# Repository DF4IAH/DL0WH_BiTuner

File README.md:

# DL0WH_BiTuner_Firmware
Based on the DJ0ABR tuner hardware this project is a replacement for the controller PCB and its firmware. The new PCB does have a __STM32L476RGT6__ MCU device and has got preparations for SWR metering.

## V1.2 PCB after placement and routing was done:

## V1.2 MCU Pinout:

## Ready for samples:
The board is again ready for production.

## Version list:
V1.2 SWD connector bad size - 2019-02-01
* Library content for the CORTEX JTAG/SWD connector was wrong, fixed.
* PCB board house failed on trace distances of 6 mils. Design expanded to 8 mils.

---

V1.1 LQFP64 bug fix - 2019-01-18
* Due to a bad LQFP64 package within the STM32L4 library (who made that crappy library?) the device did not fit at the PCB. That made a turn-around to take time and money. Never trust any library again.

---

V1.0 initial version - 2019-01-04

---

73  Uli DF4IAH, Ladenburg, 2019-02-01

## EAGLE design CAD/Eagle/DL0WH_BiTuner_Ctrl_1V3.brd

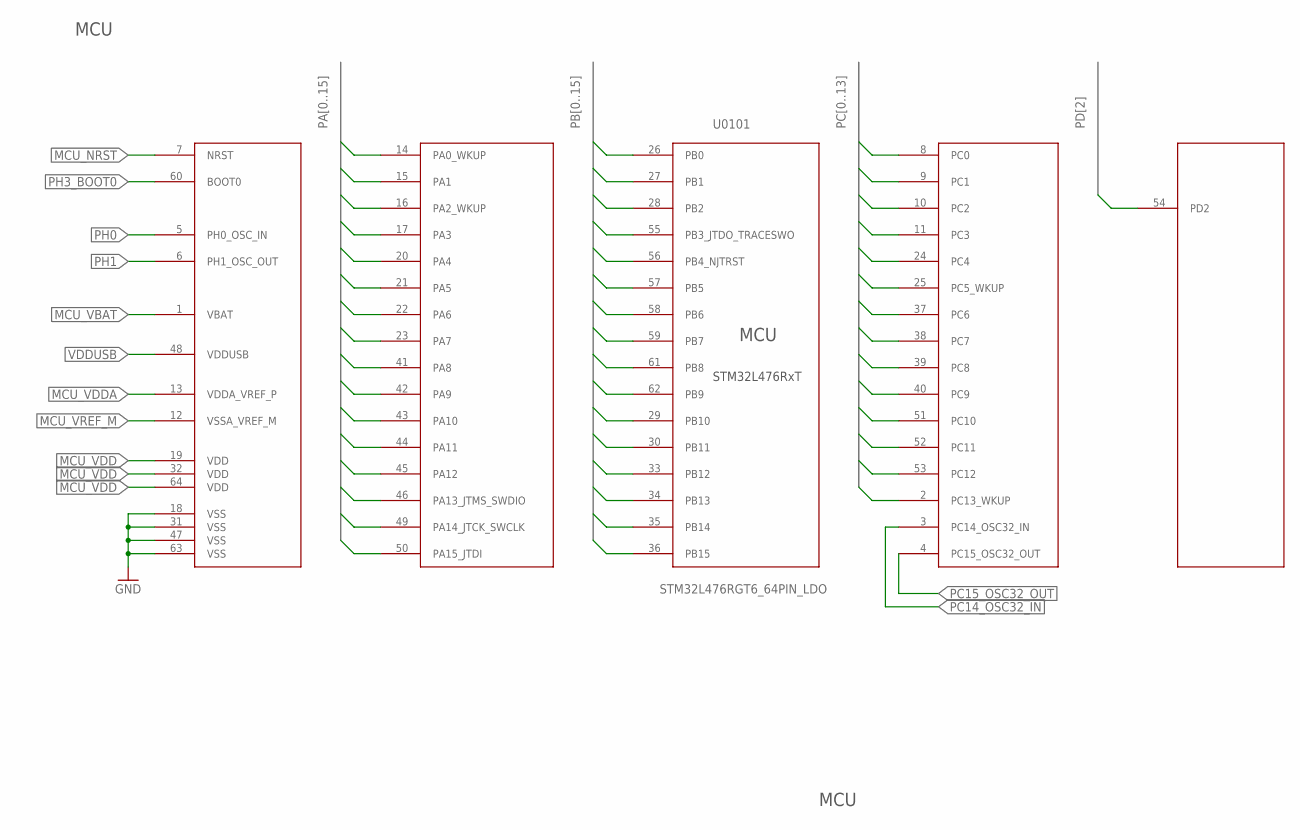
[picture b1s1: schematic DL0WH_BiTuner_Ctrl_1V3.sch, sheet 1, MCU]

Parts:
U0101: STM32L476RGT6_64PIN_LDO; LQFP64

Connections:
GND: U0101.18 (VSS), U0101.31 (VSS), U0101.47 (VSS), U0101.63 (VSS); also elsewhere on the board
MCU_NRST: U0101.7 (NRST); also elsewhere on the board
MCU_VBAT: U0101.1 (VBAT); also elsewhere on the board
MCU_VDD: U0101.19 (VDD), U0101.32 (VDD), U0101.64 (VDD); also elsewhere on the board
MCU_VDDA: U0101.13 (VDDA_VREF_P); also elsewhere on the board
MCU_VREF_M: U0101.12 (VSSA_VREF_M); also elsewhere on the board
PA0: U0101.14 (PA0_WKUP); also elsewhere on the board
PA1: U0101.15 (PA1); also elsewhere on the board
PA2: U0101.16 (PA2_WKUP)
PA3: U0101.17 (PA3); also elsewhere on the board
PA4: U0101.20 (PA4)
PA5: U0101.21 (PA5); also elsewhere on the board
PA6: U0101.22 (PA6); also elsewhere on the board
PA7: U0101.23 (PA7); also elsewhere on the board
PA8: U0101.41 (PA8)
PA9: U0101.42 (PA9); also elsewhere on the board
PA10: U0101.43 (PA10); also elsewhere on the board
PA11: U0101.44 (PA11); also elsewhere on the board
PA12: U0101.45 (PA12); also elsewhere on the board
PA13: U0101.46 (PA13_JTMS_SWDIO); also elsewhere on the board
PA14: U0101.49 (PA14_JTCK_SWCLK); also elsewhere on the board
PA15: U0101.50 (PA15_JTDI); also elsewhere on the board
PB0: U0101.26 (PB0); also elsewhere on the board
PB1: U0101.27 (PB1); also elsewhere on the board
PB2: U0101.28 (PB2); also elsewhere on the board
PB3: U0101.55 (PB3_JTDO_TRACESWO)
PB4: U0101.56 (PB4_NJTRST)
PB5: U0101.57 (PB5)
PB6: U0101.58 (PB6); also elsewhere on the board
PB7: U0101.59 (PB7); also elsewhere on the board
PB8: U0101.61 (PB8)
PB9: U0101.62 (PB9); also elsewhere on the board
PB10: U0101.29 (PB10); also elsewhere on the board
PB11: U0101.30 (PB11); also elsewhere on the board
PB12: U0101.33 (PB12); also elsewhere on the board
PB13: U0101.34 (PB13); also elsewhere on the board
PB14: U0101.35 (PB14)
PB15: U0101.36 (PB15)
PC0: U0101.8 (PC0); also elsewhere on the board
PC1: U0101.9 (PC1); also elsewhere on the board
PC2: U0101.10 (PC2); also elsewhere on the board
PC3: U0101.11 (PC3); also elsewhere on the board
PC4: U0101.24 (PC4); also elsewhere on the board
PC5: U0101.25 (PC5_WKUP)
PC6: U0101.37 (PC6)
PC7: U0101.38 (PC7)
PC8: U0101.39 (PC8)
PC9: U0101.40 (PC9)
PC10: U0101.51 (PC10)
PC11: U0101.52 (PC11)
PC12: U0101.53 (PC12)
PC13: U0101.2 (PC13_WKUP)
PC14_OSC32_IN: U0101.3 (PC14_OSC32_IN); also elsewhere on the board
PC15_OSC32_OUT: U0101.4 (PC15_OSC32_OUT); also elsewhere on the board
PD2: U0101.54 (PD2)
PH0: U0101.5 (PH0_OSC_IN)
PH1: U0101.6 (PH1_OSC_OUT)
PH3_BOOT0: U0101.60 (BOOT0); also elsewhere on the board
VDDUSB: U0101.48 (VDDUSB); also elsewhere on the board

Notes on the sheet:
STM32L476RxT
MCU

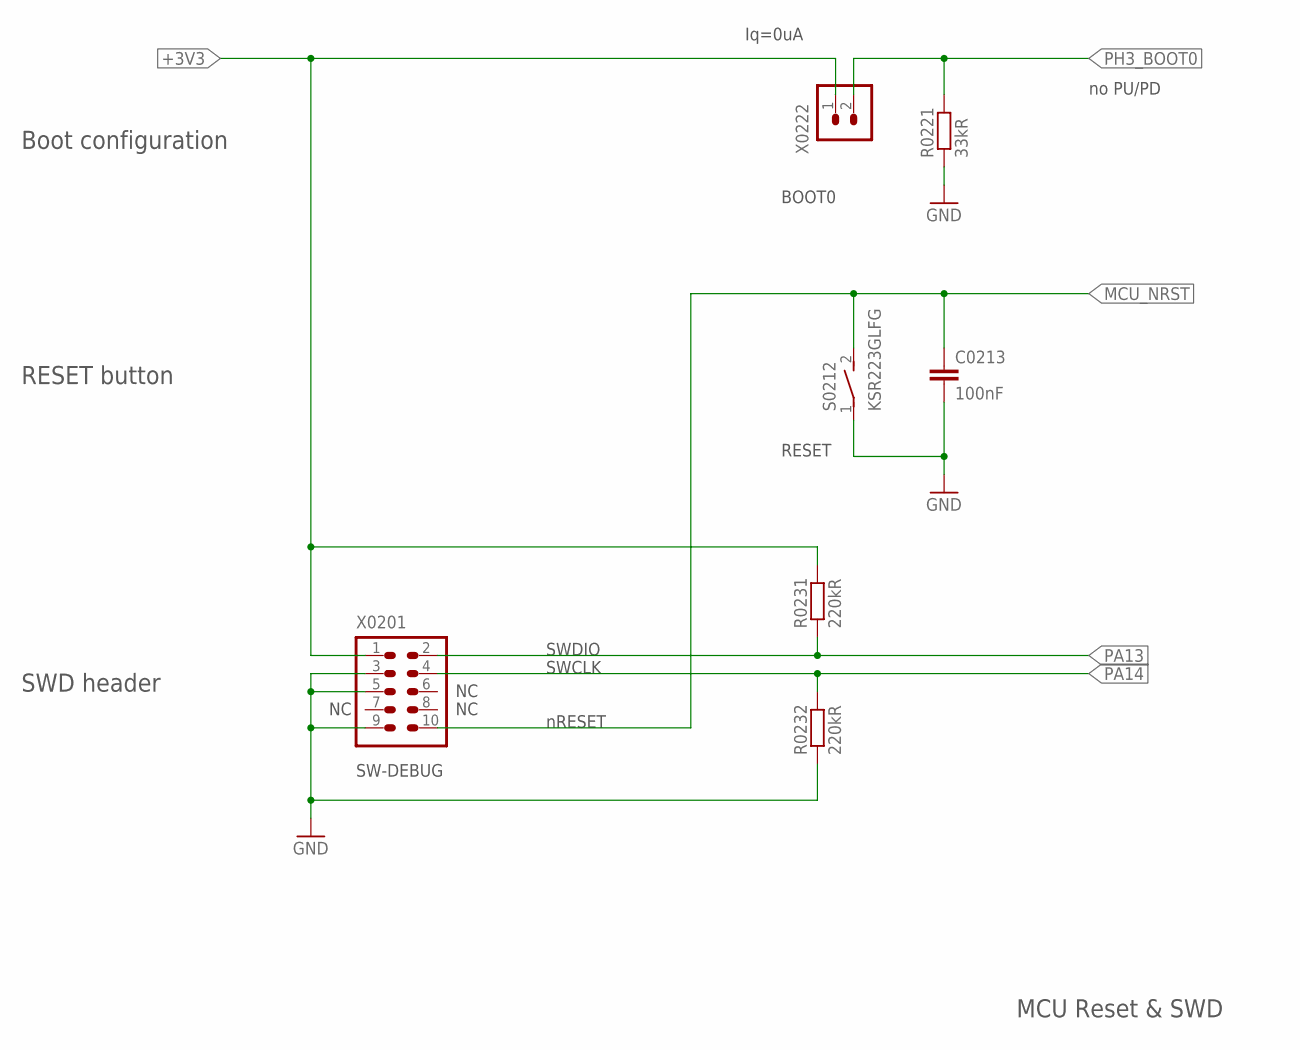
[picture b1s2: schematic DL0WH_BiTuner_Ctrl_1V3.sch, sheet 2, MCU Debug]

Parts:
C0213: 100nF; C0402
R0221: 33kR; R0402
R0231, R0232: 220kR; R0402
S0212: KSR223GLFG; KSR223G_SMD_1POL
X0201: FTSH-105-01-F-D-K; 2X05_1MM27_SHROUDED_CORTEX_JTAG_SWD
X0222: HEADER-1X2; 1X02

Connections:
+3V3: R0231.2, X0201.1, X0222.1; also elsewhere on the board
GND: C0213.2, R0221.1, R0232.1, S0212.1, X0201.3, X0201.5, X0201.9; also elsewhere on the board
MCU_NRST: C0213.1, S0212.2 (S), X0201.10; also elsewhere on the board
PA13: R0231.1, X0201.2; also elsewhere on the board
PA14: R0232.2, X0201.4; also elsewhere on the board
PH3_BOOT0: R0221.2, X0222.2; also elsewhere on the board

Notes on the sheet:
SWDIO
SWCLK
RESET
BOOT0
SW-DEBUG
SWD header
Boot configuration
RESET button
nRESET
MCU Reset & SWD
no PU/PD
Iq=0uA

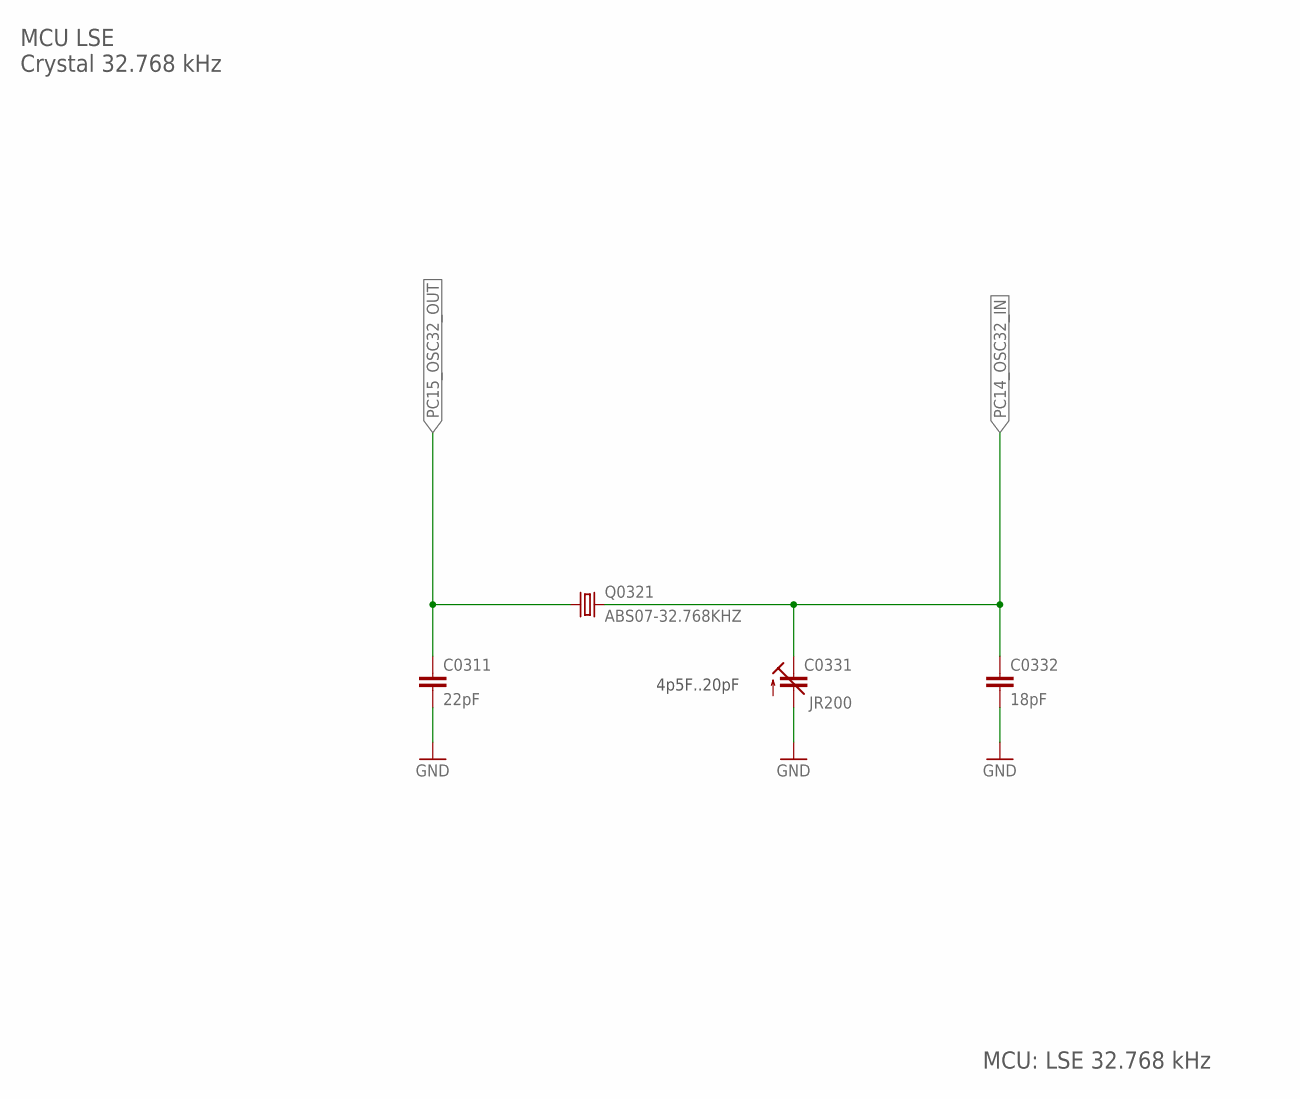
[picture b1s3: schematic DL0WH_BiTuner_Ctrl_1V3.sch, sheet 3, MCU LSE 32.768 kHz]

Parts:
C0311: 22pF; C0402
C0331: JR200; 3MM2_X_2MM5
C0332: 18pF; C0402
Q0321: ABS07-32.768KHZ; ABS07

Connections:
GND: C0311.2, C0331.+ (A), C0332.2; also elsewhere on the board
PC14_OSC32_IN: C0331.- (E), C0332.1, Q0321.2; also elsewhere on the board
PC15_OSC32_OUT: C0311.1, Q0321.1; also elsewhere on the board

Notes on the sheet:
4p5F..20pF
MCU LSE Crystal 32.768 kHz
MCU: LSE 32.768 kHz

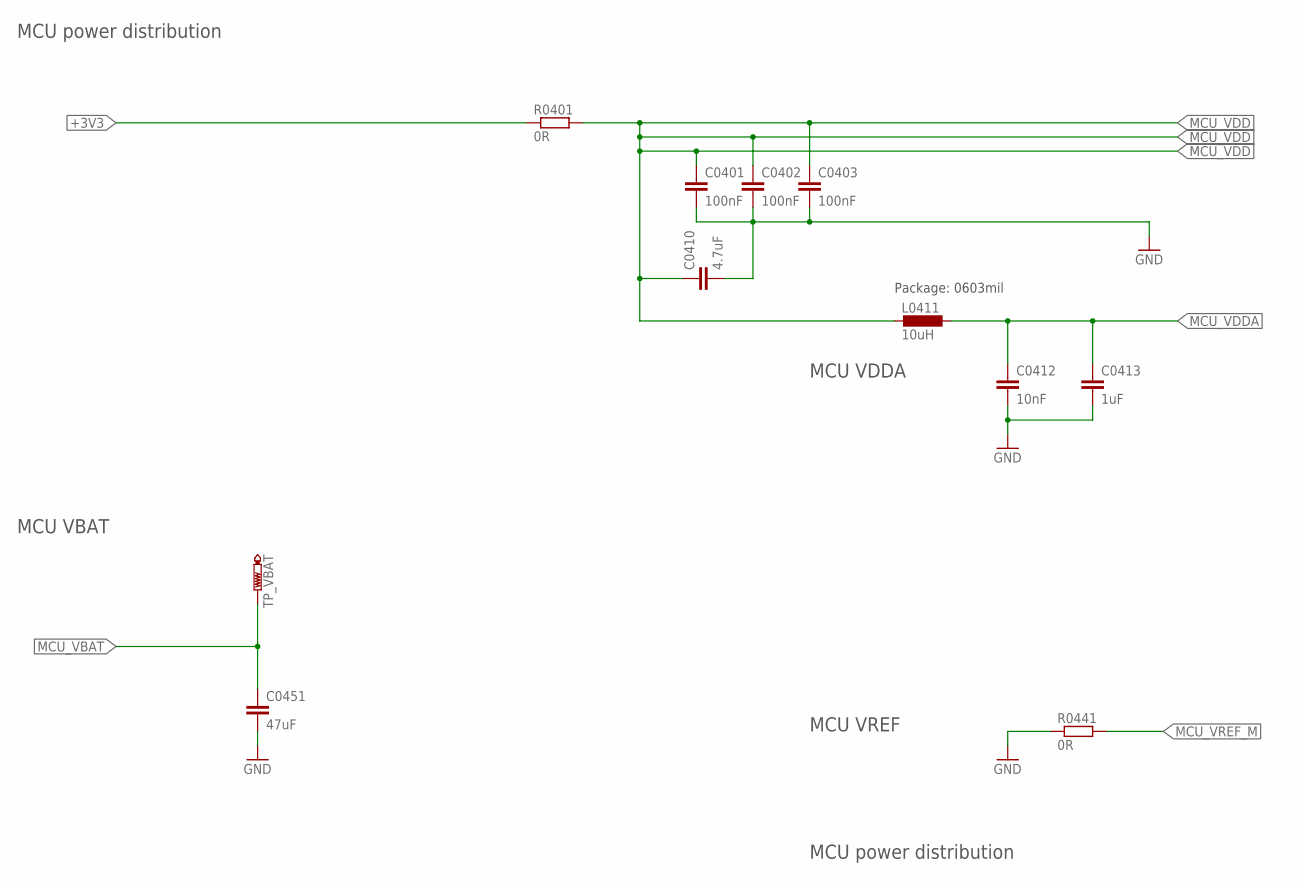
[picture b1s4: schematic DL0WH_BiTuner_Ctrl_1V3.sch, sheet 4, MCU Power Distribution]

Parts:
C0401, C0402, C0403: 100nF; C0402
C0410: 4.7uF; C0603
C0412: 10nF; C0402
C0413: 1uF; C0402
C0451: 47uF; C0805
L0411: 10uH; L0603
R0401, R0441: 0R; R0402
TP_VBAT: PTR1B1,27; B1,27

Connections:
+3V3: R0401.1; also elsewhere on the board
GND: C0401.2, C0402.2, C0403.2, C0410.2, C0412.2, C0413.2, C0451.2, R0441.1; also elsewhere on the board
MCU_VBAT: C0451.1, TP_VBAT.TP; also elsewhere on the board
MCU_VDD: C0401.1, C0402.1, C0403.1, C0410.1, L0411.1, R0401.2; also elsewhere on the board
MCU_VDDA: C0412.1, C0413.1, L0411.2; also elsewhere on the board
MCU_VREF_M: R0441.2; also elsewhere on the board

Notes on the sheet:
MCU VDDA
MCU VREF
MCU VBAT
MCU power distribution
Package: 0603mil

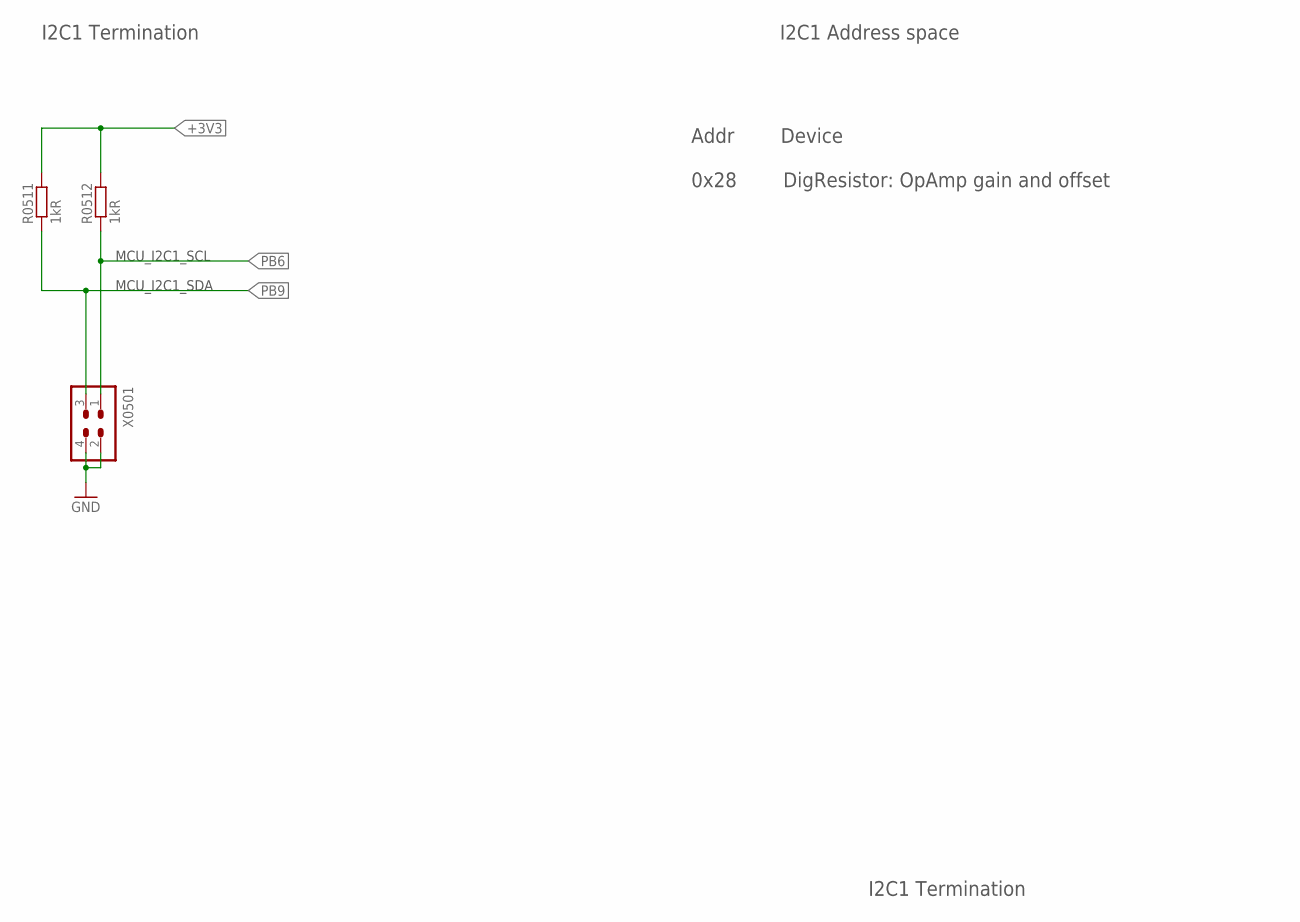
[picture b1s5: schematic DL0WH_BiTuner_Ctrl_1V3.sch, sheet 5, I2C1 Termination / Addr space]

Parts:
R0511, R0512: 1kR; R0402
X0501: HEADER-2X2; 2X02

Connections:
+3V3: R0511.2, R0512.2; also elsewhere on the board
GND: X0501.2, X0501.4; also elsewhere on the board
PB6: R0512.1, X0501.1; also elsewhere on the board
PB9: R0511.1, X0501.3; also elsewhere on the board

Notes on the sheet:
Addr Device 0x28 DigResistor: OpAmp gain and offset
I2C1 Termination
I2C1 Address space
MCU_I2C1_SCL
MCU_I2C1_SDA

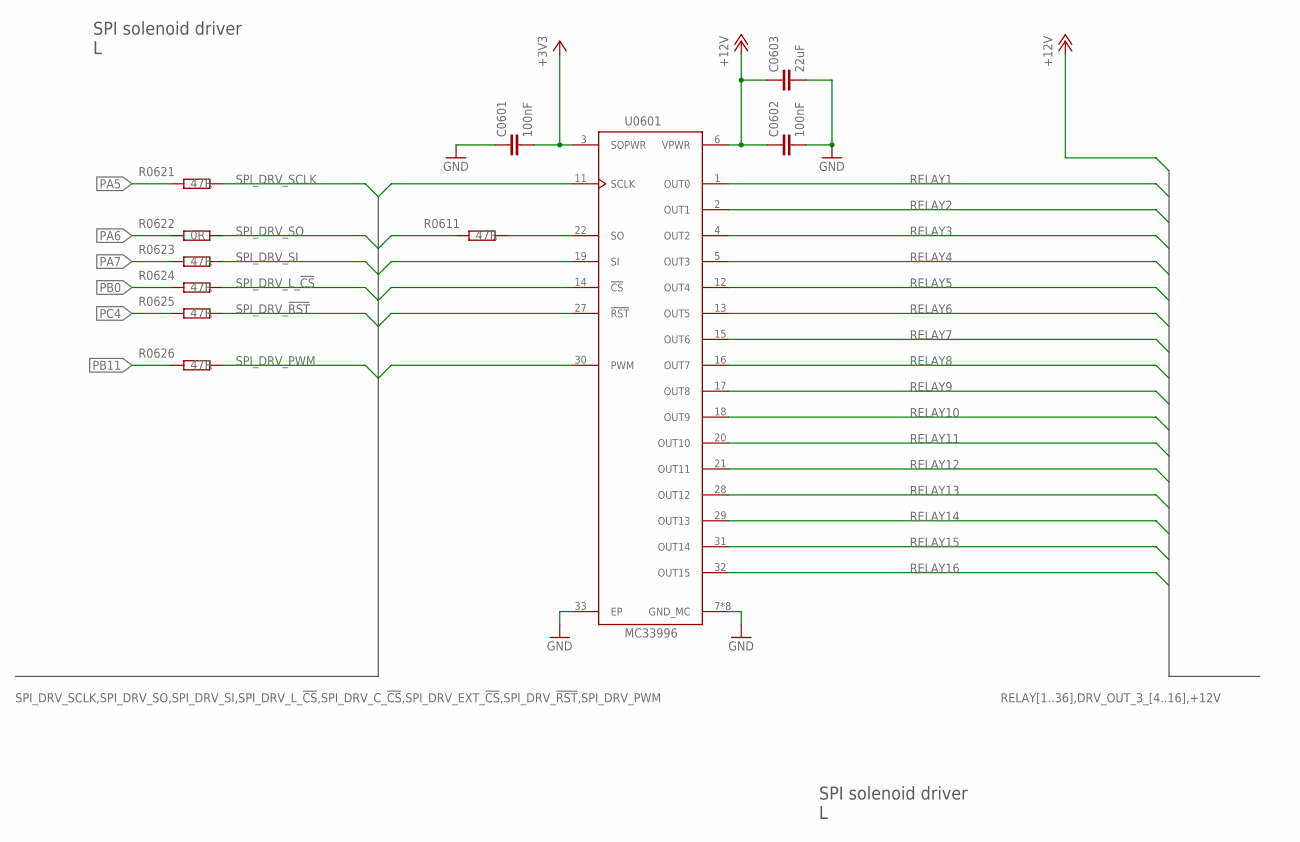
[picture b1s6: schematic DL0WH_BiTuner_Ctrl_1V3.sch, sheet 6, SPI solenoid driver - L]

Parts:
C0601, C0602: 100nF; C0402
C0603: 22uF; C0603
R0611, R0621, R0623, R0624, R0625, R0626: 47R; R0402
R0622: 0R; R0402
U0601: MC33996; SOICW32

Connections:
+3V3: C0601.2, U0601.3 (SOPWR); also elsewhere on the board
+12V: C0602.1, C0603.1, U0601.6 (VPWR); also elsewhere on the board
GND: C0601.1, C0602.2, C0603.2, U0601.7 (GND_MC), U0601.8 (GND_MC), U0601.9 (GND_MC), U0601.10 (GND_MC), U0601.23 (GND_MC), U0601.24 (GND_MC), U0601.25 (GND_MC), U0601.26 (GND_MC), U0601.33 (EP); also elsewhere on the board
unnamed: R0611.2, U0601.22 (SO)
PA5: R0621.1; also elsewhere on the board
PA6: R0622.1; also elsewhere on the board
PA7: R0623.1; also elsewhere on the board
PB0: R0624.1; also elsewhere on the board
PB11: R0626.1; also elsewhere on the board
PC4: R0625.1; also elsewhere on the board
RELAY1: U0601.1 (OUT0); also elsewhere on the board
RELAY2: U0601.2 (OUT1); also elsewhere on the board
RELAY3: U0601.4 (OUT2); also elsewhere on the board
RELAY4: U0601.5 (OUT3); also elsewhere on the board
RELAY5: U0601.12 (OUT4); also elsewhere on the board
RELAY6: U0601.13 (OUT5); also elsewhere on the board
RELAY7: U0601.15 (OUT6); also elsewhere on the board
RELAY8: U0601.16 (OUT7); also elsewhere on the board
RELAY9: U0601.17 (OUT8); also elsewhere on the board
RELAY10: U0601.18 (OUT9); also elsewhere on the board
RELAY11: U0601.20 (OUT10); also elsewhere on the board
RELAY12: U0601.21 (OUT11); also elsewhere on the board
RELAY13: U0601.28 (OUT12); also elsewhere on the board
RELAY14: U0601.29 (OUT13); also elsewhere on the board
RELAY15: U0601.31 (OUT14); also elsewhere on the board
RELAY16: U0601.32 (OUT15); also elsewhere on the board
SPI_DRV_!RST: R0625.2, U0601.27 (!RST); also elsewhere on the board
SPI_DRV_L_!CS: R0624.2, U0601.14 (!CS)
SPI_DRV_PWM: R0626.2, U0601.30 (PWM); also elsewhere on the board
SPI_DRV_SCLK: R0621.2, U0601.11 (SCLK); also elsewhere on the board
SPI_DRV_SI: R0623.2, U0601.19 (SI); also elsewhere on the board
SPI_DRV_SO: R0611.1, R0622.2; also elsewhere on the board

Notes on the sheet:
SPI solenoid driver L

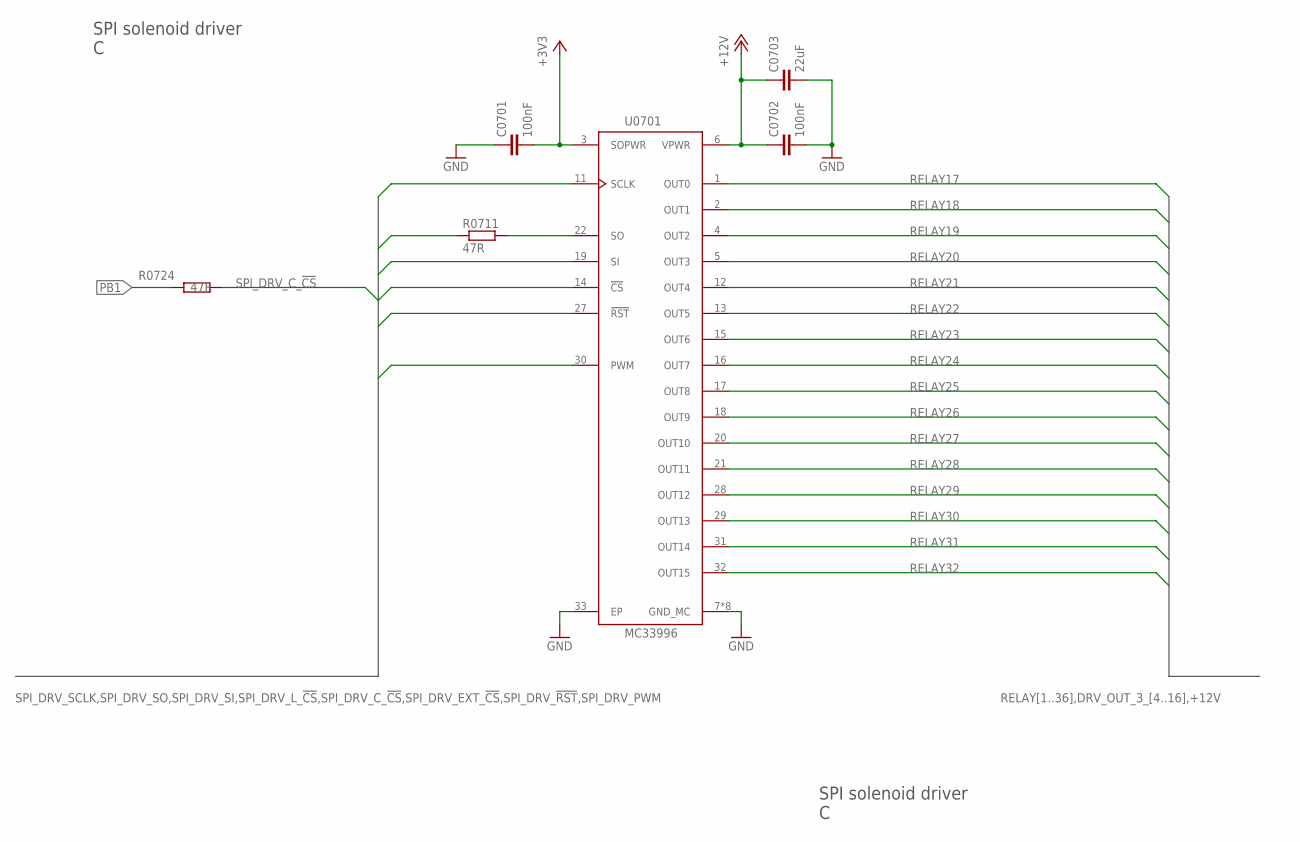
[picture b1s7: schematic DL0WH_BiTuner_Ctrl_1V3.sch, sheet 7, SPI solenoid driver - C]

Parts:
C0701, C0702: 100nF; C0402
C0703: 22uF; C0603
R0711, R0724: 47R; R0402
U0701: MC33996; SOICW32

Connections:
+3V3: C0701.2, U0701.3 (SOPWR); also elsewhere on the board
+12V: C0702.1, C0703.1, U0701.6 (VPWR); also elsewhere on the board
GND: C0701.1, C0702.2, C0703.2, U0701.7 (GND_MC), U0701.8 (GND_MC), U0701.9 (GND_MC), U0701.10 (GND_MC), U0701.23 (GND_MC), U0701.24 (GND_MC), U0701.25 (GND_MC), U0701.26 (GND_MC), U0701.33 (EP); also elsewhere on the board
unnamed: R0711.2, U0701.22 (SO)
PB1: R0724.1; also elsewhere on the board
RELAY17: U0701.1 (OUT0); also elsewhere on the board
RELAY18: U0701.2 (OUT1); also elsewhere on the board
RELAY19: U0701.4 (OUT2); also elsewhere on the board
RELAY20: U0701.5 (OUT3); also elsewhere on the board
RELAY21: U0701.12 (OUT4); also elsewhere on the board
RELAY22: U0701.13 (OUT5); also elsewhere on the board
RELAY23: U0701.15 (OUT6); also elsewhere on the board
RELAY24: U0701.16 (OUT7); also elsewhere on the board
RELAY25: U0701.17 (OUT8); also elsewhere on the board
RELAY26: U0701.18 (OUT9); also elsewhere on the board
RELAY27: U0701.20 (OUT10); also elsewhere on the board
RELAY28: U0701.21 (OUT11); also elsewhere on the board
RELAY29: U0701.28 (OUT12); also elsewhere on the board
RELAY30: U0701.29 (OUT13); also elsewhere on the board
RELAY31: U0701.31 (OUT14); also elsewhere on the board
RELAY32: U0701.32 (OUT15); also elsewhere on the board
SPI_DRV_!RST: U0701.27 (!RST); also elsewhere on the board
SPI_DRV_C_!CS: R0724.2, U0701.14 (!CS)
SPI_DRV_PWM: U0701.30 (PWM); also elsewhere on the board
SPI_DRV_SCLK: U0701.11 (SCLK); also elsewhere on the board
SPI_DRV_SI: U0701.19 (SI); also elsewhere on the board
SPI_DRV_SO: R0711.1; also elsewhere on the board

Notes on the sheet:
SPI solenoid driver C

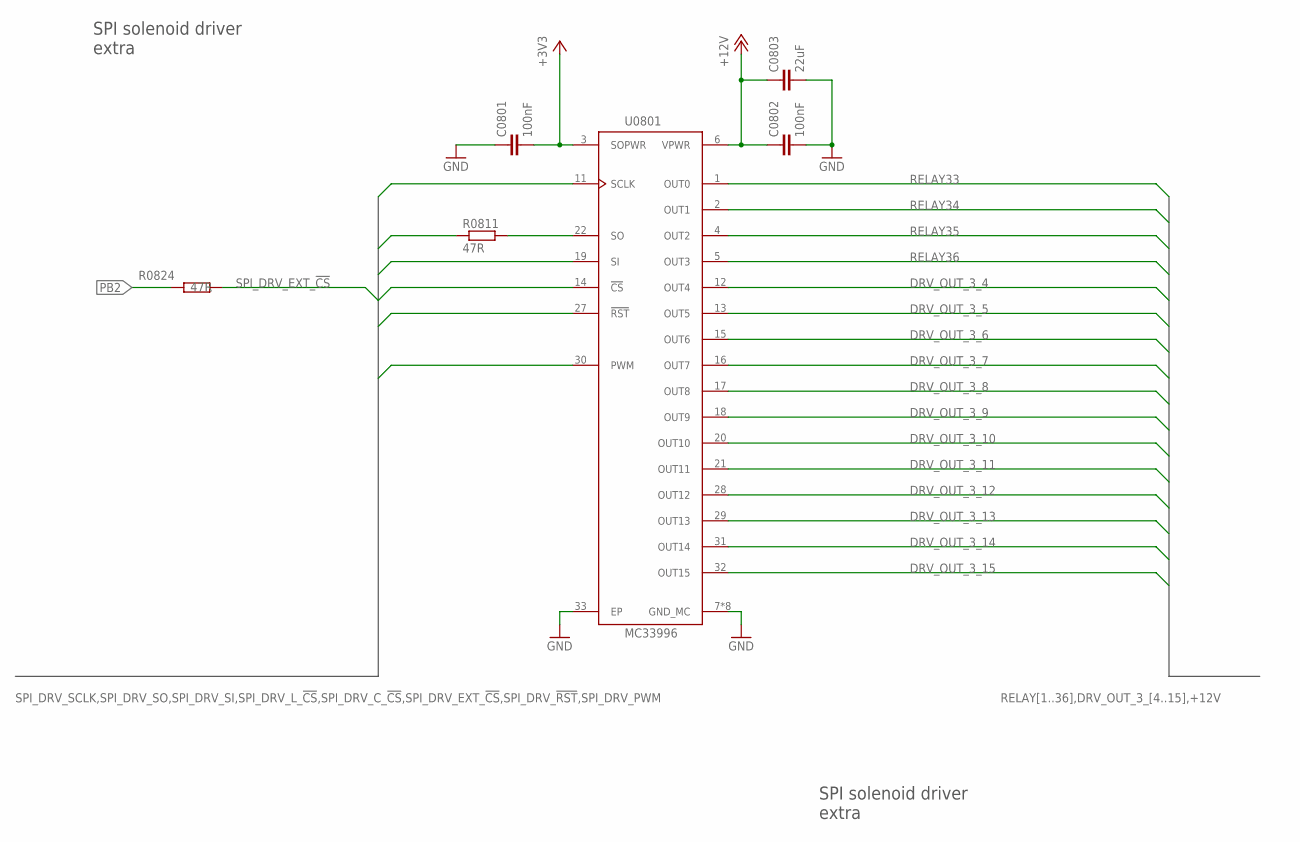
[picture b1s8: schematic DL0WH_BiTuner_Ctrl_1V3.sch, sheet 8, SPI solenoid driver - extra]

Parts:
C0801, C0802: 100nF; C0402
C0803: 22uF; C0603
R0811, R0824: 47R; R0402
U0801: MC33996; SOICW32

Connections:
+3V3: C0801.2, U0801.3 (SOPWR); also elsewhere on the board
+12V: C0802.1, C0803.1, U0801.6 (VPWR); also elsewhere on the board
DRV_OUT_3_4: U0801.12 (OUT4)
DRV_OUT_3_5: U0801.13 (OUT5)
DRV_OUT_3_6: U0801.15 (OUT6)
DRV_OUT_3_7: U0801.16 (OUT7)
DRV_OUT_3_8: U0801.17 (OUT8)
DRV_OUT_3_9: U0801.18 (OUT9)
DRV_OUT_3_10: U0801.20 (OUT10)
DRV_OUT_3_11: U0801.21 (OUT11)
DRV_OUT_3_12: U0801.28 (OUT12)
DRV_OUT_3_13: U0801.29 (OUT13)
DRV_OUT_3_14: U0801.31 (OUT14)
DRV_OUT_3_15: U0801.32 (OUT15)
GND: C0801.1, C0802.2, C0803.2, U0801.7 (GND_MC), U0801.8 (GND_MC), U0801.9 (GND_MC), U0801.10 (GND_MC), U0801.23 (GND_MC), U0801.24 (GND_MC), U0801.25 (GND_MC), U0801.26 (GND_MC), U0801.33 (EP); also elsewhere on the board
unnamed: R0811.2, U0801.22 (SO)
PB2: R0824.1; also elsewhere on the board
RELAY33: U0801.1 (OUT0); also elsewhere on the board
RELAY34: U0801.2 (OUT1); also elsewhere on the board
RELAY35: U0801.4 (OUT2); also elsewhere on the board
RELAY36: U0801.5 (OUT3); also elsewhere on the board
SPI_DRV_!RST: U0801.27 (!RST); also elsewhere on the board
SPI_DRV_EXT_!CS: R0824.2, U0801.14 (!CS)
SPI_DRV_PWM: U0801.30 (PWM); also elsewhere on the board
SPI_DRV_SCLK: U0801.11 (SCLK); also elsewhere on the board
SPI_DRV_SI: U0801.19 (SI); also elsewhere on the board
SPI_DRV_SO: R0811.1; also elsewhere on the board

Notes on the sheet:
SPI solenoid driver extra

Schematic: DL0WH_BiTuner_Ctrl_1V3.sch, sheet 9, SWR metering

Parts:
C0901, C0911, C0945: 1nF; C0402
C0921, C0951, C0952, C0962: 100nF; C0402
C0941, C0943: 22uF; C0603
C0942: 2.2uF; C0603
C0963: 100pF; C0402
D0942: CRS08; SOD80C
D0951, D0971: CMAD6001; SOD923
L0901, L0911: 10uH; L0603
L0941, L0943: 20uH; L1812
R0901, R0911: 2kR; R0402
R0902, R0912, R0961, R0962, R0972: 1kR; R0402
R0903, R0913: 15kR; R0402
R0904, R0914: 150kR; R0402
R0921, R0922: 47R; R0402
R0923: 2MR; R0402
R0945: 8.2kR; R0402
R0946: 33kR; R0402
R0963: 20kR; R0402
R0971: 10kR; R0402
U0921: TS5A23166; R-PDSO-G8
U0941: LM2611; SOT95P280X145-5N
U0951, U0961: OPA354; SOT-23-5
U0962: MCP4661-103E-MS; TSSOP14

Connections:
+3V3: C0921.1, C0941.1, C0951.1, C0962.1, L0941.2, R0904.2, R0914.2, R0971.1, U0921.8, U0941.4 (!SHDN), U0941.5 (VIN), U0951.5 (V+), U0961.5 (V+), U0962.8 (P0A), U0962.11 (!WP), U0962.14 (VDD); also elsewhere on the board
-1V5: C0943.1, C0945.2, C0952.1, L0943.1, R0945.2, U0951.2 (V-), U0961.2 (V-)
GND: C0901.2, C0911.2, C0921.2, C0941.2, C0943.2, C0951.2, C0952.2, C0962.2, D0942.C, D0971.C, R0902.1, R0912.1, R0923.1, R0946.1, U0921.4, U0941.2 (GND), U0951.3 (+IN), U0961.3 (+IN), U0962.1 (HVC/A0), U0962.4 (VSS), U0962.12 (A2), U0962.13 (A1); also elsewhere on the board
LM2611_NFB: C0945.1, R0945.1, R0946.2, U0941.3 (NFB)
LM2611_SW: C0942.1, L0941.1, U0941.1 (SW)
LM_DA: C0942.2, D0942.A, L0943.2
OPA_FB: R0963.1, U0962.7 (P1A)
OPA_PULL: R0962.2, U0962.9 (P0W)
PA3: R0922.1; also elsewhere on the board
PB6: U0962.2 (SCL); also elsewhere on the board
PB9: U0962.3 (SDA); also elsewhere on the board
PC0: R0972.2; also elsewhere on the board
PC2: D0971.A, R0971.2; also elsewhere on the board
PC3: R0921.1; also elsewhere on the board
RM_FWD: L0901.2; also elsewhere on the board
RM_REV: L0911.2; also elsewhere on the board
SWR_IN_FWD: R0903.2, R0904.1, U0921.1
SWR_IN_FWD_HI: C0901.1, L0901.1, R0901.1
SWR_IN_FWD_LO: R0901.2, R0902.2, R0903.1
SWR_IN_REV: R0913.2, R0914.1, U0921.5
SWR_IN_REV_HI: C0911.1, L0911.1, R0911.1
SWR_IN_REV_LO: R0911.2, R0912.2, R0913.1
SWR_OP1_OUT: D0951.C, R0961.1, U0951.1 (OUT)
SWR_OP2_IN: C0963.1, R0961.2, R0962.1, U0961.4 (-IN), U0962.6 (P1W)
SWR_OP2_OUT: C0963.2, R0963.2, R0972.1, U0961.1 (OUT)
SWR_SEL_FWD: R0921.2, U0921.7
SWR_SEL_PWR: D0951.A, R0923.2, U0921.2, U0921.6, U0951.4 (-IN)
SWR_SEL_REV: R0922.2, U0921.3

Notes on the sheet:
SWR metering
SWR_ADC
FWD / REV switch
Logarithmic Amp I2C1 addr: 0x28
SWR_TEMP
PMIC -1.5V Cuk
Reference diode
MCU_I2C1_SCL
MCU_I2C1_SDA
nom: 5.0kR
nom: 4.9kR

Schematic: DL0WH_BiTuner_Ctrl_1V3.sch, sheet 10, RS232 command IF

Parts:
C1001, C1002, C1003, C1004, C1005: 1uF; C0402
C1051, C1052, C1053, C1054: 10nF; C0402
R1001, R1002, R1003, R1004: 47R; R0402
U1001: MAX232_SOIC16; SOIC16N
X1051, X1052, X1053: WIRE-TO-BOARD_5MM08_1X02

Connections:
+5V: C1001.1, U1001.16 (VCC); also elsewhere on the board
GND: C1001.2, C1004.2, C1005.2, C1051.2, C1052.2, C1053.2, C1054.2, U1001.15 (GND), X1052.1, X1052.2; also elsewhere on the board
MP_RS_CTS_R: R1003.2, U1001.10 (T2IN)
MP_RS_RTR_R: R1004.2, U1001.9 (R2OUT)
MP_RS_RXD_R: R1001.2, U1001.11 (T1IN)
MP_RS_TXD_R: R1002.2, U1001.12 (R1OUT)
PB10: R1002.1; also elsewhere on the board
PB12: R1003.1; also elsewhere on the board
PB13: R1004.1; also elsewhere on the board
PC1: R1001.1; also elsewhere on the board
RS_DTE_CTS: C1053.1, U1001.7 (T2OUT), X1053.1
RS_DTE_RTR: C1054.1, U1001.8 (R2IN), X1053.2
RS_DTE_RXD: C1051.1, U1001.14 (T1OUT), X1051.1
RS_DTE_TXD: C1052.1, U1001.13 (R1IN), X1051.2
RS_MX_C1N1: C1002.2, U1001.3 (C1-)
RS_MX_C1P: C1002.1, U1001.1 (C1+)
RS_MX_C2M1: C1003.2, U1001.5 (C2-)
RS_MX_C2P: C1003.1, U1001.4 (C2+)
RS_MX_VM: C1005.1, U1001.6 (V-)
RS_MX_VP: C1004.1, U1001.2 (V+)

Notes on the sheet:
RS232 command interface (V24)
RS232 command IF
RS232 TXD
RS232 CTS
RS232 GND
RS232 RXD
RS232 RTR
Use LF filters at BiTuner box connector !
---- 100 uH ---- | | 10nF 100nF | | GND GND

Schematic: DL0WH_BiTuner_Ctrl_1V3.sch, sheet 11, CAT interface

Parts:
C1101, C1102, C1103, C1104, C1105: 1uF; C0402
C1151, C1152, C1153, C1154: 10nF; C0402
R1101, R1102, R1103, R1104: 47R; R0402
U1101: MAX232_SOIC16; SOIC16N
X1151, X1152, X1153: WIRE-TO-BOARD_5MM08_1X02

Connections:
+5V: C1101.1, U1101.16 (VCC); also elsewhere on the board
CAT_DTE_CTS: C1153.1, U1101.7 (T2OUT), X1153.1
CAT_DTE_RTR: C1154.1, U1101.8 (R2IN), X1153.2
CAT_DTE_RXD: C1151.1, U1101.14 (T1OUT), X1151.1
CAT_DTE_TXD: C1152.1, U1101.13 (R1IN), X1151.2
CAT_MX_C1N: C1102.2, U1101.3 (C1-)
CAT_MX_C1P: C1102.1, U1101.1 (C1+)
CAT_MX_C2M: C1103.2, U1101.5 (C2-)
CAT_MX_C2P: C1103.1, U1101.4 (C2+)
CAT_MX_VM: C1105.1, U1101.6 (V-)
CAT_MX_VP: C1104.1, U1101.2 (V+)
GND: C1101.2, C1104.2, C1105.2, C1151.2, C1152.2, C1153.2, C1154.2, U1101.15 (GND), X1152.1, X1152.2; also elsewhere on the board
MP_CAT_CTS_R: R1103.2, U1101.10 (T2IN)
MP_CAT_RTR_R: R1104.2, U1101.9 (R2OUT)
MP_CAT_RXD_R: R1101.2, U1101.11 (T1IN)
MP_CAT_TXD_R: R1102.2, U1101.12 (R1OUT)
PA0: R1101.1; also elsewhere on the board
PA1: R1102.1; also elsewhere on the board
PA15: R1103.1; also elsewhere on the board
PB7: R1104.1; also elsewhere on the board

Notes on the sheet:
CAT interface (V24)
CAT interface
CAT TXD
CAT CTS
CAT GND
CAT RXD
CAT RTR
Use LF filters at BiTuner box connector !
---- 100 uH ---- | | 10nF 100nF | | GND GND

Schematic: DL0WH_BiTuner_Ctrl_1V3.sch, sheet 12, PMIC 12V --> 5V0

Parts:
C1201, C1202, C1203: 10uF; C0603
C1204: 10nF; C0402
C1205: 3.3uF; C0603
C1211: 0.47uF; C0402
C1212: 100nF; C0402
C1221, C1222, C1223: 22uF; C0603
D1221: CRS08; SOD80C
L1211: 2.2uH; L_6.00MM_X_6.00MM
R1211: 3R; R0402
U1201: LM53603-Q1; HTSSOP16
X1211: WIRE-TO-BOARD_5MM08_1X02

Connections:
+5V: C1221.1, C1222.1, C1223.1, D1221.C, L1211.1, R1211.2, U1201.9 (FB); also elsewhere on the board
+12V: C1201.1, C1202.1, C1203.1, C1204.1, U1201.11 (EN), U1201.12 (VIN), U1201.13 (VIN), X1211.1; also elsewhere on the board
GND: C1201.2, C1202.2, C1203.2, C1204.2, C1205.1, C1212.2, C1221.2, C1222.2, C1223.2, U1201.6 (SYNC), U1201.7 (FPWM), U1201.10 (AGND), U1201.15 (PGND), U1201.16 (PGND), U1201.PAD (EP), U1201.PAD1 (EP), U1201.PAD2 (EP), U1201.PAD3 (EP), U1201.PAD4 (EP), U1201.PAD5 (EP), U1201.PAD6 (EP), U1201.PAD7 (EP), U1201.PAD8 (EP), U1201.PAD9 (EP), U1201.PAD10 (EP), U1201.PAD11 (EP), U1201.PAD12 (EP), U1201.PAD13 (EP), X1211.2; also elsewhere on the board
LM53603_!RESET: U1201.8 (!RESET)
LM53603_BIAS: C1212.1, R1211.1, U1201.5 (BIAS)
LM53603_CBOOT: C1211.2, U1201.3 (CBOOT)
LM53603_SW: C1211.1, L1211.2, U1201.1 (SW), U1201.2 (SW)
LM53603_VCC: C1205.2, U1201.4 (VCC)
VDDUSB: D1221.A; also elsewhere on the board

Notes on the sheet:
PMIC 12V --> 5V0
12V Down-Converter
Iq=24uA
Abracon ASPI-6045S-2R2N-T 6.0mm x 6.0mm

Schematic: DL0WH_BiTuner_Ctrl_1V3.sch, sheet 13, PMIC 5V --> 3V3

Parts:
C1301, C1311: 22uF; C0603
L1311: 10uH; L_4.50MM_X_3.20MM
R1301: 100kR; R0402
R1302: 220kR; R0402
R1321, R1322: 1MR; R0402
U1301: TPS62056; S-PDSO-G10

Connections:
+3V3: C1311.1, L1311.1, L1311.3 (1), R1321.2, R1322.2, U1301.5 (FB); also elsewhere on the board
+5V: C1301.1, R1302.2, U1301.1 (VIN), U1301.8 (EN); also elsewhere on the board
GND: C1301.2, C1311.2, R1301.1, U1301.3 (VSS), U1301.7 (SYNC), U1301.10 (PGND); also elsewhere on the board
TPS_LBI: R1301.2, R1302.1, U1301.6 (LBI)
TPS_LBO: R1322.1, U1301.2 (LBO)
TPS_PG: R1321.1, U1301.4 (PG)
TPS_SW: L1311.2, L1311.4 (2), U1301.9 (SW)

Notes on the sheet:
PMIC 5V --> 3V3
TPS_PG
TPS_LBO
MURATA LQH43PN100M26L 4.5mm x 3.2mm (1812)

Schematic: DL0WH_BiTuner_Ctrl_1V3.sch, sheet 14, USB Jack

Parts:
C1403: 1nF; C0402
PF1411: 1.1A/2.2A; M1206
R1402: 330kR; R0402
X1401: MOLEX 105017-0001; USB-B-MICRO-SMD_MOLEX-105017-0001

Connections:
GND: C1403.1, R1402.1, X1401.GND; also elsewhere on the board
PA9: PF1411.1, X1401.VBUS (J_VUSB); also elsewhere on the board
PA10: X1401.ID (J_ID); also elsewhere on the board
PA11: X1401.D- (J_D-); also elsewhere on the board
PA12: X1401.D+ (J_D+); also elsewhere on the board
USB_SHIELD: C1403.2, R1402.2, X1401.JSHIELD (SHIELD), X1401.JSHIELD@2 (SHIELD), X1401.JSHIELD@3 (SHIELD), X1401.JSHIELD@4 (SHIELD), X1401.JSHIELD@5 (SHIELD), X1401.JSHIELD@6 (SHIELD)
VDDUSB: PF1411.2; also elsewhere on the board

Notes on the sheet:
Impedance 90 Ohms
USB device and USB host (OTG) interface
MCU_USB_OTG_FS_DM
MCU_USB_OTG_FS_DP
MCU_USB_OTG_FS_ID
MCU_USB_OTG_FS_VBUS
LITTLEFUSE 1206L050YR

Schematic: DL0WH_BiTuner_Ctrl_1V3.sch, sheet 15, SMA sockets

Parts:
X1501: SMA_SMT_AMPHENOL-901-143; SMA_SMT_AMPHENOL_901-143
X1511: SAMTEC SMA-J-P-H-RA-TH1; SMA_SMT_AMPHENOL_901-143

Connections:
GND: X1501.2, X1501.3 (2), X1501.4 (2), X1501.5 (2), X1511.2, X1511.3 (2), X1511.4 (2), X1511.5 (2); also elsewhere on the board
RM_FWD: X1501.1; also elsewhere on the board
RM_REV: X1511.1; also elsewhere on the board

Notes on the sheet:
SMA direct. coupler FWD
SMA direct. coupler REV

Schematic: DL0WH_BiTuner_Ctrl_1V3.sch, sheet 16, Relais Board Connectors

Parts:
X1601, X1602: 2X10_2MM56_SOCKET; 2X10

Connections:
+12V: X1602.17, X1602.18, X1602.19, X1602.20; also elsewhere on the board
RELAY1: X1601.1; also elsewhere on the board
RELAY2: X1601.2; also elsewhere on the board
RELAY3: X1601.3; also elsewhere on the board
RELAY4: X1601.4; also elsewhere on the board
RELAY5: X1601.5; also elsewhere on the board
RELAY6: X1601.6; also elsewhere on the board
RELAY7: X1601.7; also elsewhere on the board
RELAY8: X1601.8; also elsewhere on the board
RELAY9: X1601.9; also elsewhere on the board
RELAY10: X1601.10; also elsewhere on the board
RELAY11: X1601.11; also elsewhere on the board
RELAY12: X1601.12; also elsewhere on the board
RELAY13: X1601.13; also elsewhere on the board
RELAY14: X1601.14; also elsewhere on the board
RELAY15: X1601.15; also elsewhere on the board
RELAY16: X1601.16; also elsewhere on the board
RELAY17: X1601.17; also elsewhere on the board
RELAY18: X1601.18; also elsewhere on the board
RELAY19: X1601.19; also elsewhere on the board
RELAY20: X1601.20; also elsewhere on the board
RELAY21: X1602.1; also elsewhere on the board
RELAY22: X1602.2; also elsewhere on the board
RELAY23: X1602.3; also elsewhere on the board
RELAY24: X1602.4; also elsewhere on the board
RELAY25: X1602.5; also elsewhere on the board
RELAY26: X1602.6; also elsewhere on the board
RELAY27: X1602.7; also elsewhere on the board
RELAY28: X1602.8; also elsewhere on the board
RELAY29: X1602.9; also elsewhere on the board
RELAY30: X1602.10; also elsewhere on the board
RELAY31: X1602.11; also elsewhere on the board
RELAY32: X1602.12; also elsewhere on the board
RELAY33: X1602.13; also elsewhere on the board
RELAY34: X1602.14; also elsewhere on the board
RELAY35: X1602.15; also elsewhere on the board
RELAY36: X1602.16; also elsewhere on the board

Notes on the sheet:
Relay Connectors

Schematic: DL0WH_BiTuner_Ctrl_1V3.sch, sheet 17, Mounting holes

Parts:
H1711, H1721, H1731, H1751, H1761: MOUNT-PAD-ROUND3.0; 3,0-PAD

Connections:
GND: H1711.B3,0, H1721.B3,0, H1731.B3,0, H1751.B3,0, H1761.B3,0; also elsewhere on the board

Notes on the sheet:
Mounting holes
